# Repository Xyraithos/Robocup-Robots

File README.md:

# Robocup-Robots
This contains basics for circuitry, schematic and code for robocup mini size robot team. 
This file consists of 2 parts: PCB docs and Arduino codes.

# PCB_Robocup docs

Robocup12313.brd file is the drawn circuit file with using one sided copper as board. Back side of copper is purposefully left blank for changes, additions to system.
This board designed to fit 10x10x10 cm^3 limitations. Please note that it is not a full square and also works as a layer in robot itself.

Robocup12313.sch file is the schematic file for connections of Arduino NANO, TB6612FNG, NRF24L01 and several switches&capacitors. 

# !!! Please check and note the manually jumping points in board. Hence it uses only one side, it requires several manual jumping points. !!!

# Ard Codes docs

client.ino is the code file for individual robots to be deployed.

server.ino is the code file for master machine of individual robots.

Mustafa ALKIN

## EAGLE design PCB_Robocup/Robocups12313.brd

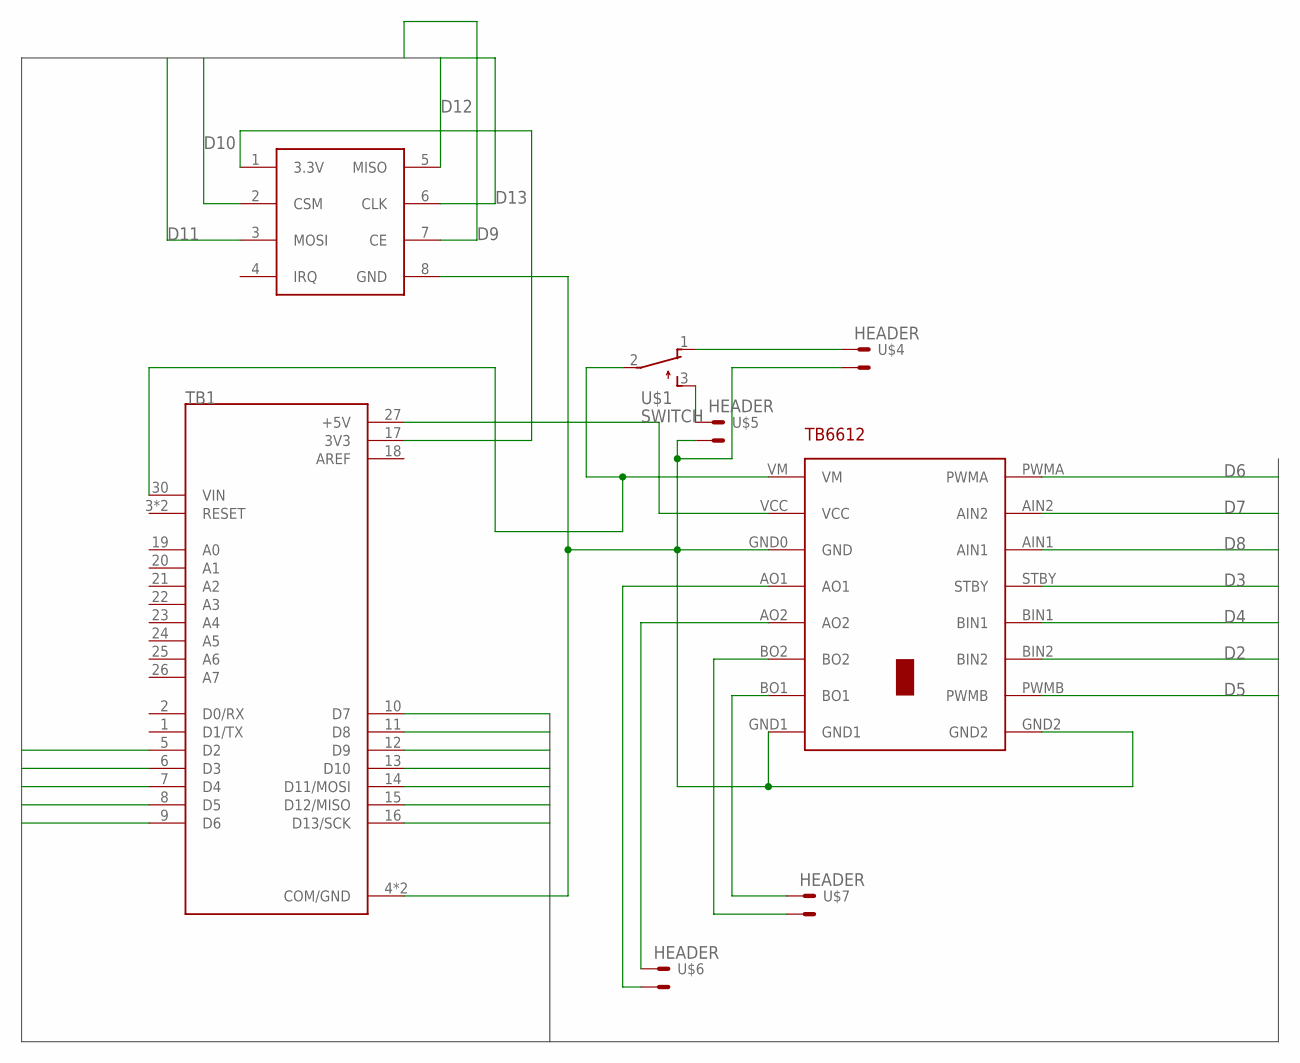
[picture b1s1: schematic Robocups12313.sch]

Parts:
TB1: ARDUINO_NANO; SHIELD_ARDUINO_NANO
U$1: SWITCH; 255SB
U$2: TB6612; TB6612FNG
U$3: NRF
U$4, U$5, U$6, U$7: HEADER; 22-23-2021

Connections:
AREF: TB1.18 (AREF)
D2: TB1.5 (D2), U$2.BIN2
D3: TB1.6 (D3), U$2.STBY
D4: TB1.7 (D4), U$2.BIN1
D5: TB1.8 (D5), U$2.PWMB
D6: TB1.9 (D6), U$2.PWMA
D7: TB1.10 (D7), U$2.AIN2
D8: TB1.11 (D8), U$2.AIN1
D9: TB1.12 (D9), U$3.7 (CE)
D10: TB1.13 (D10), U$3.2 (CSM)
D11: TB1.14 (D11/MOSI), U$3.3 (MOSI)
D12: TB1.15 (D12/MISO), U$3.5 (MISO)
D13: TB1.16 (D13/SCK), U$3.6 (CLK)
unnamed: U$2.BO1, U$7.1 (S)
unnamed: U$1.1 (O), U$4.1 (S)
unnamed: U$2.AO2, U$6.1 (S)
unnamed: TB1.4 (COM/GND), TB1.29 (COM/GND), U$2.GND0 (GND), U$2.GND1, U$2.GND2, U$3.8 (GND), U$4.2 (S1), U$5.2 (S1)
unnamed: U$1.3 (S), U$5.1 (S)
unnamed: TB1.30 (VIN), U$1.2, U$2.VM
unnamed: TB1.27 (+5V), U$2.VCC
unnamed: TB1.17 (3V3), U$3.1 (3.3V)
unnamed: U$2.BO2, U$7.2 (S1)
unnamed: U$2.AO1, U$6.2 (S1)

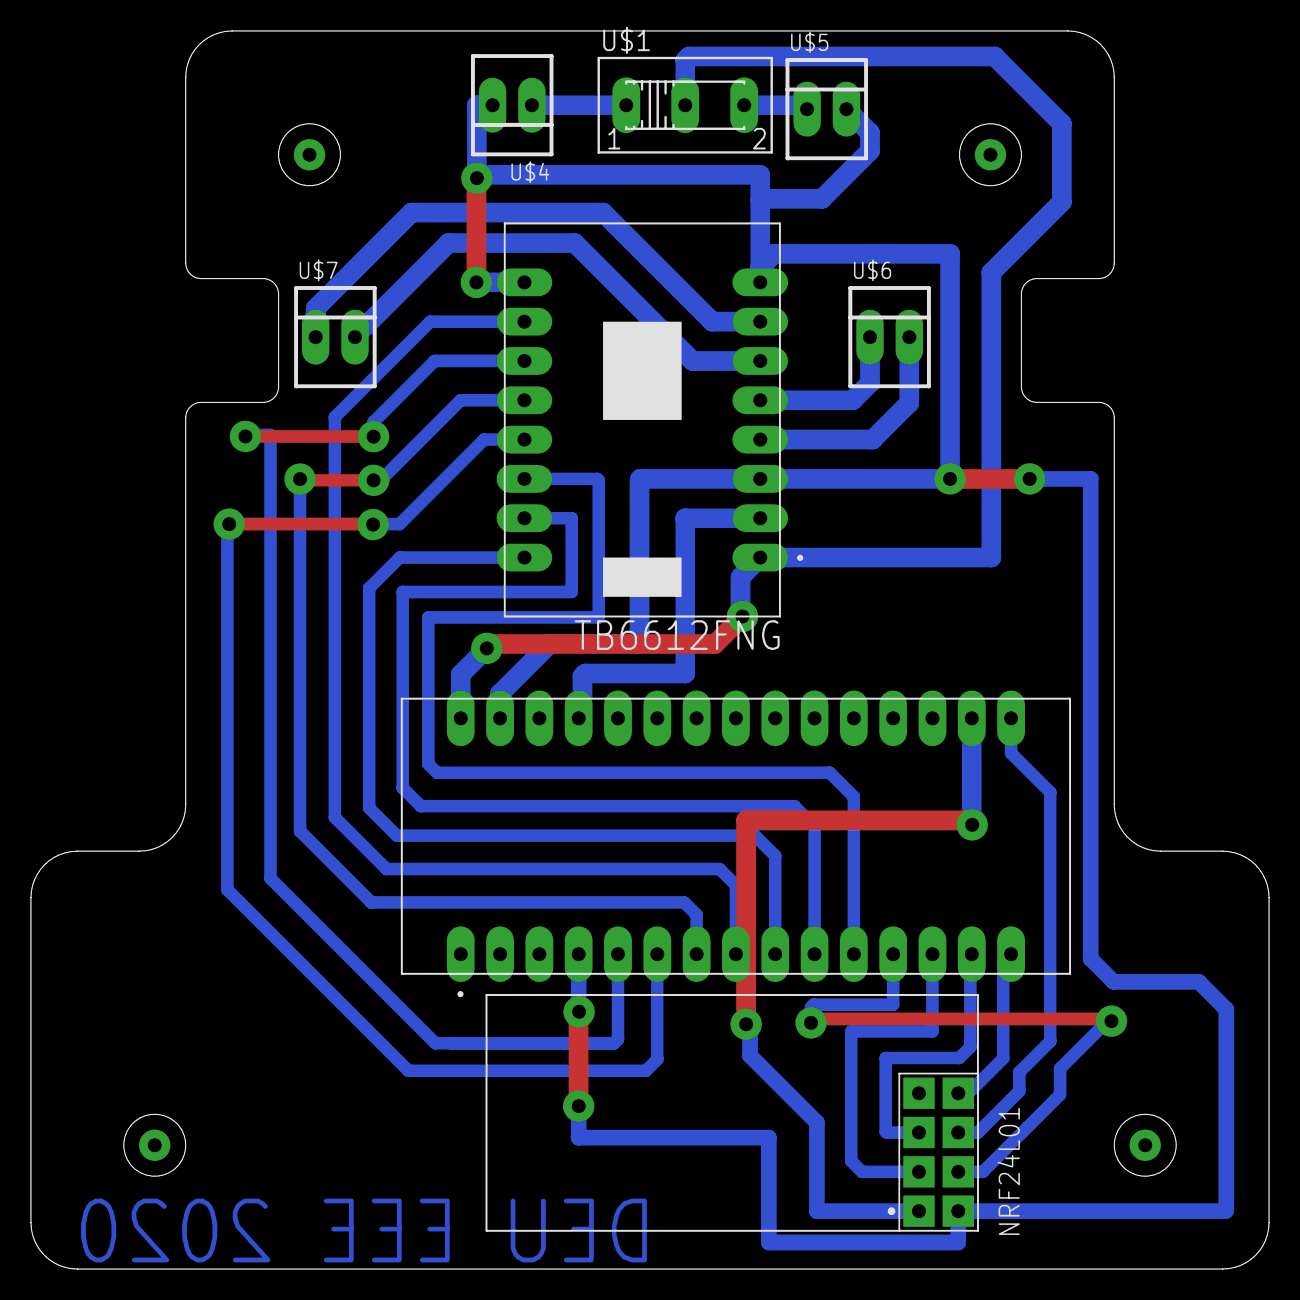
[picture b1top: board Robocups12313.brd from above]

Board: 2 copper layers, 80.0 x 80.0 mm, 8 parts (0 on the bottom side), 22 nets.

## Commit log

2021-01-14 Create Eagledocs
